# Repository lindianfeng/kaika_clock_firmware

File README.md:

# kaika clock firmware
stm32 led clock

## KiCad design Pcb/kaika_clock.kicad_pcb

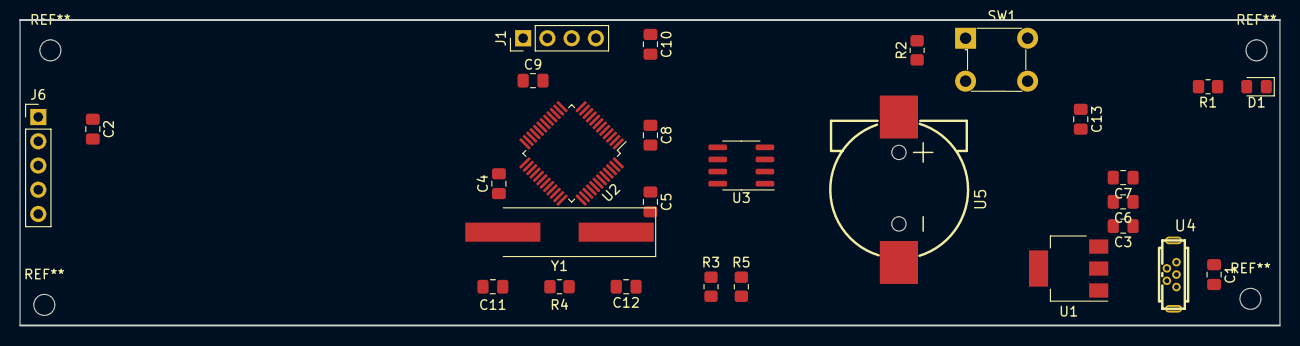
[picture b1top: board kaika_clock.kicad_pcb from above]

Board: 2 copper layers, 132.0 x 32.0 mm, 28 parts (0 on the bottom side), 19 nets, no tracks yet.

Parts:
C1, C6: 10uf; C_0805_2012Metric_Pad1.18x1.45mm_HandSolder
C2, C3, C4, C5, C7, C8, C9, C10, C13: 100nf; C_0805_2012Metric_Pad1.18x1.45mm_HandSolder
C11, C12: 20p; C_0805_2012Metric_Pad1.18x1.45mm_HandSolder
D1: LED_Small; LED_0805_2012Metric_Pad1.15x1.40mm_HandSolder
J1: Conn_01x04; PinHeader_1x04_P2.54mm_Vertical
J6: Conn_01x04; PinHeader_1x05_P2.54mm_Vertical
R1: 330; R_0805_2012Metric_Pad1.20x1.40mm_HandSolder
R2: R_Small; R_0805_2012Metric_Pad1.20x1.40mm_HandSolder
R3, R5: 0; R_0805_2012Metric_Pad1.20x1.40mm_HandSolder
R4: 1M; R_0805_2012Metric_Pad1.20x1.40mm_HandSolder
SW1: Reset; Switch_Tactile_THT_6x6mm
U1: AMS1117-3.3; SOT-223-3_TabPin2
U2: STM32F103C8Tx; LQFP-48_7x7mm_P0.5mm
U3: DS3231MZ; SOIC-8_3.9x4.9mm_P1.27mm
U4: MICRO-USB_TH; MICRO-USB-TH_MICRO-USB-A14
U5: CR1220-2; BAT-SMD_CR1220-2
Y1: Crystal; Crystal_SMD_HC49-SD_HandSoldering

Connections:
+3V3: C2.1, C4.1, C5.1, C6.1, C7.1, C8.1, C9.1, C13.1, J1.1, J6.1, R1.2, R2.1, U1.2, U2.1, U2.9, U2.24, U2.36, U2.48, U3.2
BOOT0: R3.2, U2.44
BOOT1: R5.2, U2.20
GND: C1.2, C2.2, C3.2, C4.2, C5.2, C6.2, C7.2, C8.2, C9.2, C10.1, C11.1, C12.1, C13.2, D1.1, J1.2, J6.2, R3.1, R5.1, SW1.2, U1.1, U2.8, U2.23, U2.35, U2.47, U3.5, U4.5, U4.6, U4.7, U5.2
I2C1_SCL: U2.42, U3.8
I2C1_SDA: U2.43, U3.7
unnamed: D1.2, R1.1
unnamed: U3.6, U5.1
OSC_IN: C11.2, R4.1, U2.5, Y1.2
OSC_OUT: C12.2, R4.2, U2.6, Y1.1
RESET: C10.2, R2.2, SW1.1, U2.7
SPI1_CS: J6.4, U2.18
SPI1_MOSI: J6.3, U2.17
SPI1_SCK: J6.5, U2.15
SWCLK: J1.4, U2.37
SWDIO: J1.3, U2.34
USB_DM: U2.32, U4.2
USB_DP: U2.33, U4.3
VCC: C1.1, C3.1, U1.3, U4.1

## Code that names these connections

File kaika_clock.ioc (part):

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Mcu.Name=STM32F103C(8-B)Tx
Mcu.Package=LQFP48
Mcu.UserName=STM32F103C8Tx
PA11.Mode=Device
PA11.Signal=USB_DM
PA12.Mode=Device
PA12.Signal=USB_DP
PA13.Mode=Serial_Wire
PA13.Signal=SYS_JTMS-SWDIO
PA14.Mode=Serial_Wire
PA14.Signal=SYS_JTCK-SWCLK
PA5.Mode=TX_Only_Simplex_Unidirect_Master
PA5.Signal=SPI1_SCK
PA7.Mode=TX_Only_Simplex_Unidirect_Master
PA7.Signal=SPI1_MOSI
PB0.GPIOParameters=GPIO_Label
PB0.GPIO_Label=MAX7219_CS
PB0.Signal=GPIO_Output
PB6.Mode=I2C
PB6.Signal=I2C1_SCL
PB7.Mode=I2C
PB7.Signal=I2C1_SDA
PC14-OSC32_IN.Mode=LSE-External-Oscillator
PC14-OSC32_IN.Signal=RCC_OSC32_IN
PC15-OSC32_OUT.Mode=LSE-External-Oscillator
PC15-OSC32_OUT.Signal=RCC_OSC32_OUT
PD0-OSC_IN.Mode=HSE-External-Oscillator
PD0-OSC_IN.Signal=RCC_OSC_IN
PD1-OSC_OUT.Mode=HSE-External-Oscillator
PD1-OSC_OUT.Signal=RCC_OSC_OUT
RCC.SYSCLKFreq_VALUE=72000000
RCC.SYSCLKSource=RCC_SYSCLKSOURCE_PLLCLK
board=custom

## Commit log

2020-12-10 init commit
2020-12-11 refect the max7219 code.
2020-12-11 add the sec heardbeat.
2020-12-11 flash the point.
2020-12-11 add timer support
2020-12-11 format the code.
2020-12-12 remove tim2.
2020-12-12 add usb device
2020-12-12 modify the heap max size to 0x600
2020-12-13 refect the dir.
2020-12-13 add max72xx support
2020-12-14 change to new 7219 lib
2020-12-14 fix dev num error.
2020-12-14 add HOW_COL
2020-12-14 add mdk support
2020-12-14 add tick
2020-12-14 modify the main,add update the rtc
2020-12-14 add show date
2020-12-14 add falsh point support
2020-12-14 nothing to say
2020-12-15 fix time format error
2020-12-15 add test led function.
2020-12-15 format the main.c
2020-12-15 change the date display
2020-12-15 add the font col data
2020-12-15 modify the display date format.
2020-12-17 fix error.
2020-12-17 fix the point error.
2020-12-17 add timer
2020-12-17 modify timer init.
2020-12-17 rename the project name
2020-12-21 add rtc suport
2020-12-21 add pcb
2020-12-21 add the pcb footpin lib
2020-12-22 add symbls lib
2020-12-23 change usb to micro usb
2020-12-24 modify the pcb
2020-12-25 move pcb to other project
2020-12-25 Update README.md
    kaika_clock_firmware
2021-01-02 add dht11 support
2021-01-02 add delay us func
2021-01-02 dht support
2021-01-02 add the delete file
